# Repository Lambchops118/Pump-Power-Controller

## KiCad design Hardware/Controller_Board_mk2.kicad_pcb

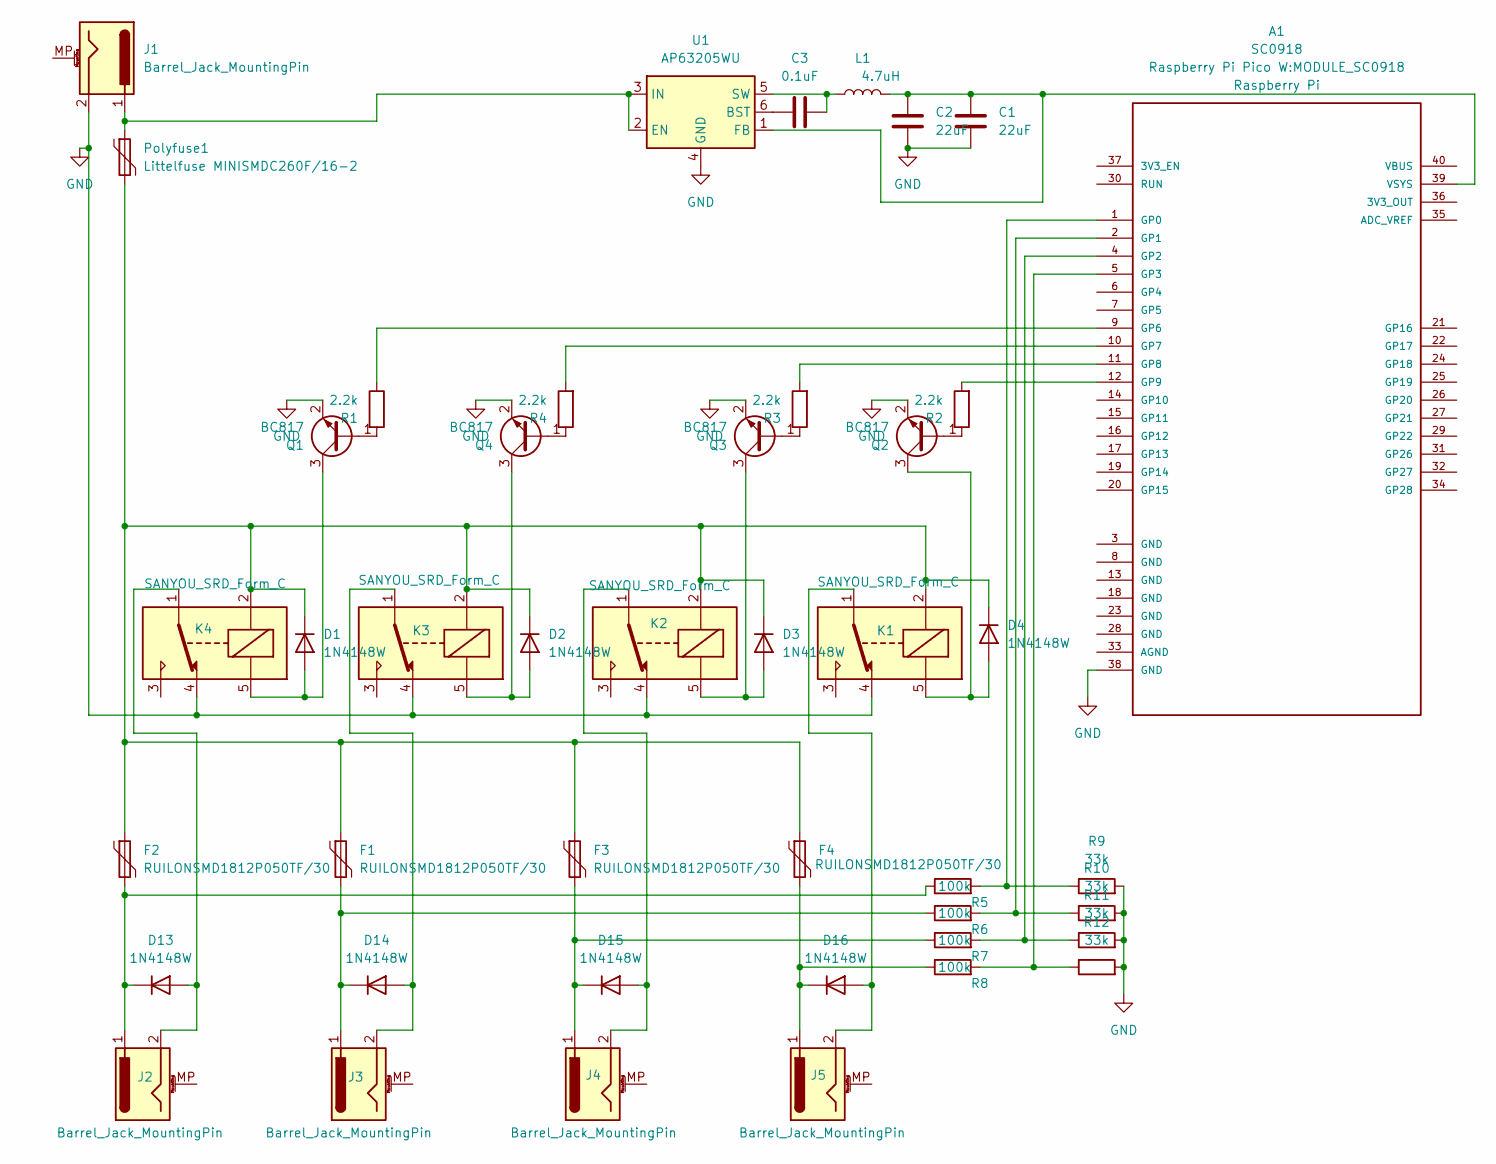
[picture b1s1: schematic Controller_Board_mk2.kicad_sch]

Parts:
A1: SC0918; MODULE_SC0918; PARTREV 1.6; LCSC C7203003
C1, C2: 22uF; R_0603_1608Metric; LCSC C59461
C3: 0.1uF; R_0603_1608Metric; LCSC C14663
D1, D2, D3, D4, D13, D14, D15, D16: 1N4148W; D_SOD-123; LCSC C81598
F1, F2, F3, F4: RUILONSMD1812P050TF/30; Fuse_1812_4532Metric; JLCPCB C12559
J1, J2, J3, J4, J5: Barrel_Jack_MountingPin; BarrelJack_CUI_PJ-102AH_Horizontal
K1, K2, K3, K4: SANYOU_SRD_Form_C; Relay_SPDT_SANYOU_SRD_Series_Form_C
L1: 4.7uH; C_1206_3216Metric; LCSC C1034
Polyfuse1: Littelfuse MINISMDC260F/16-2; Fuse_1812_4532Metric; JLCPCB C16490
Q1, Q2, Q3, Q4: BC817; SOT-23; LCSC C2145
R1, R2, R3, R4: 2.2k; R_0603_1608Metric; LCSC C4190
R5, R6, R7, R8: 100k; R_0603_1608Metric; JLCPCB C25803
R9, R10, R11, R12: 33k; R_0603_1608Metric; JLCPCB C4216
U1: AP63205WU; TSOT-23-6; LCSC C2071056

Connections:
GND: A1.38 (GND), C1.2, C2.2, J1.2, K1.4, K2.4, K3.4, K4.4, Q1.2 (E), Q2.2 (E), Q3.2 (E), Q4.2 (E), R9.2, R10.2, R11.2, R12.2, U1.4 (GND)
unnamed: A1.1 (GP0), R5.2, R9.1
unnamed: A1.2 (GP1), R6.2, R10.1
unnamed: A1.4 (GP2), R7.2, R11.1
unnamed: A1.5 (GP3), R8.2, R12.1
unnamed: A1.9 (GP6), R1.1
unnamed: A1.10 (GP7), R4.2
unnamed: A1.11 (GP8), R3.2
unnamed: A1.12 (GP9), R2.2
unnamed: A1.39 (VSYS), C1.1, C2.1, L1.2, U1.1 (FB)
unnamed: D1.2 (A), K4.5, Q1.3 (C)
unnamed: D1.1 (K), D2.1 (K), D3.1 (K), D4.1 (K), F1.1, F2.1, F3.1, F4.1, K1.2, K2.2, K3.2, K4.2, Polyfuse1.2
unnamed: D2.2 (A), K3.5, Q4.3 (C)
unnamed: D3.2 (A), K2.5, Q3.3 (C)
unnamed: D4.2 (A), K1.5, Q2.3 (C)
unnamed: D13.2 (A), J2.2, K4.1
unnamed: D13.1 (K), F2.2, J2.1, R5.1
unnamed: D14.2 (A), J3.2, K3.1
unnamed: D14.1 (K), F1.2, J3.1, R6.1
unnamed: D15.2 (A), J4.2, K2.1
unnamed: D15.1 (K), F3.2, J4.1, R7.1
unnamed: D16.2 (A), J5.2, K1.1
unnamed: D16.1 (K), F4.2, J5.1, R8.1
unnamed: Q1.1 (B), R1.2
unnamed: Q2.1 (B), R2.1
unnamed: Q3.1 (B), R3.1
unnamed: Q4.1 (B), R4.1
unnamed: C3.1, U1.6 (BST)
unnamed: J1.1, Polyfuse1.1, U1.2 (EN), U1.3 (IN)
unnamed: C3.2, L1.1, U1.5 (SW)

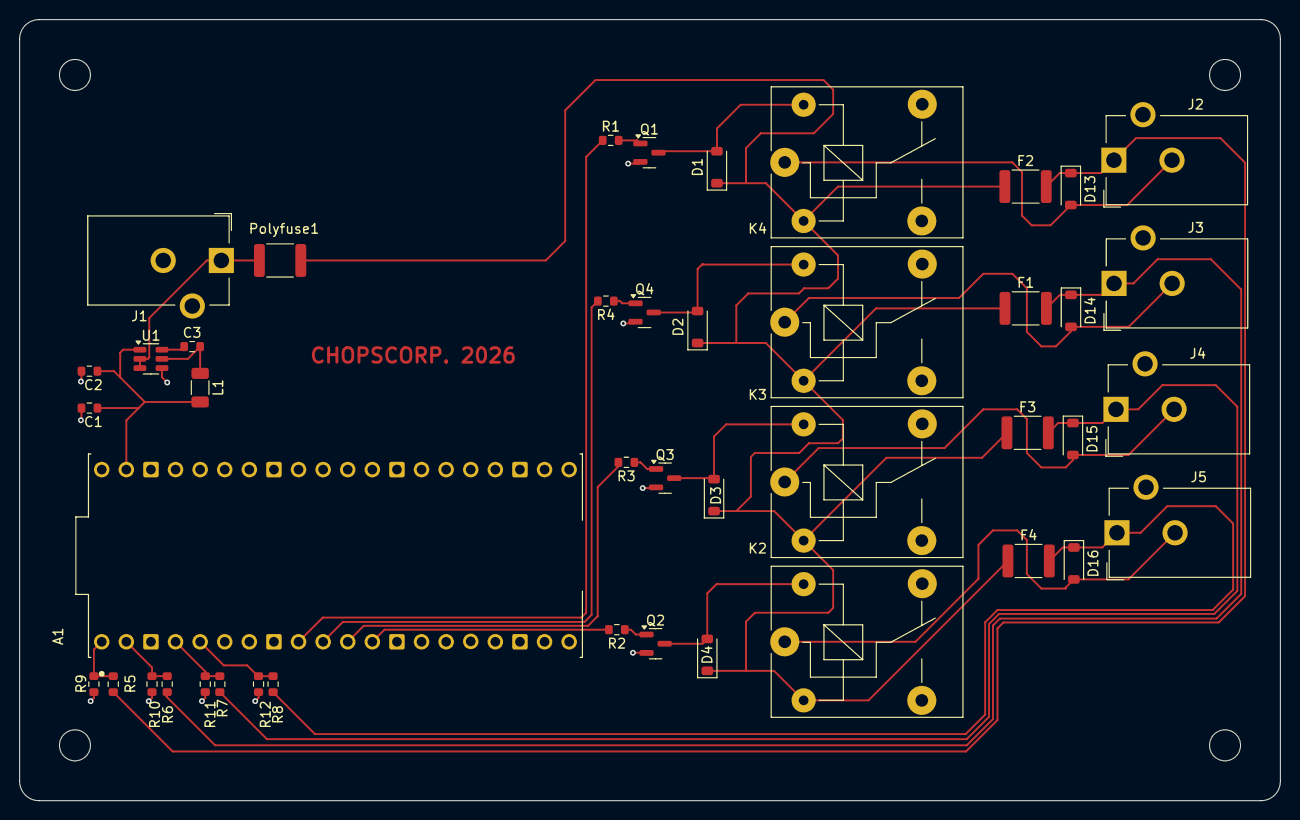
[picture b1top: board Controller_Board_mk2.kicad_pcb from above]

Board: 2 copper layers, 130.2 x 80.6 mm, 44 parts (0 on the bottom side), 30 nets.
